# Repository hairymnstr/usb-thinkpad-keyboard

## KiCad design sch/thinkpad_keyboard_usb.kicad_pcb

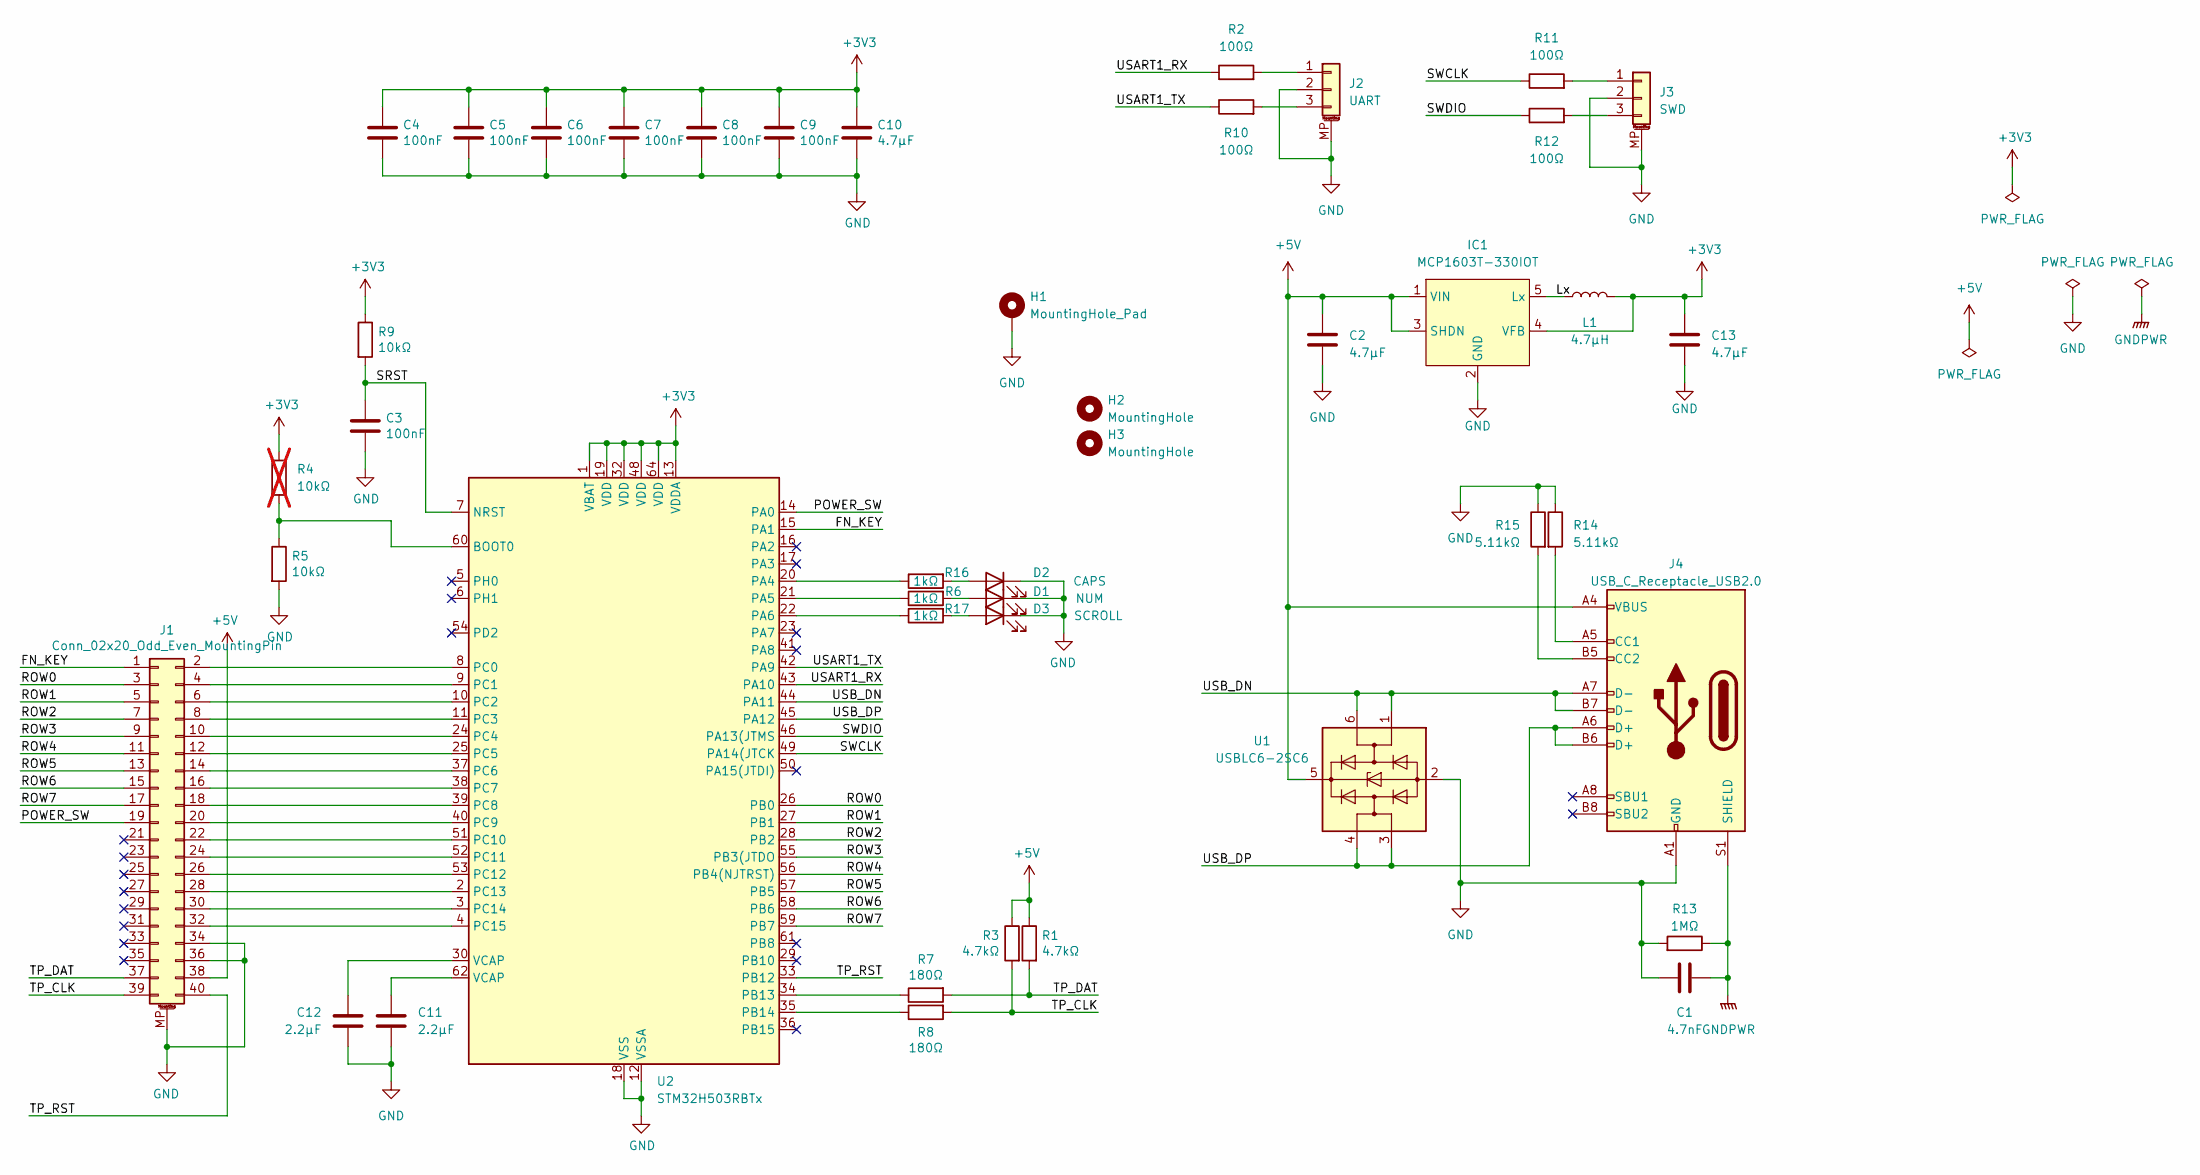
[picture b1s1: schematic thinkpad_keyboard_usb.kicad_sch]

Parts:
C1: 4.7nF; C_0805_2012Metric
C2, C10, C13: 4.7µF; C_0805_2012Metric
C3, C4, C5, C6, C7, C8, C9: 100nF; C_0603_1608Metric
C11, C12: 2.2µF; C_0603_1608Metric
D1: NUM; D_0603_1608Metric
D2: CAPS; D_0603_1608Metric
D3: SCROLL; D_0603_1608Metric
H1: MountingHole_Pad; MountingHole_2.2mm_M2_Pad
H2, H3: MountingHole; MountingHole_3.2mm_M3
IC1: MCP1603T-330IOT; TSOT-23-5
J1: Conn_02x20_Odd_Even_MountingPin; MOLEX_SLIMSTACK_54363_02x20_P0.5mm
J2: UART; JST_SH_SM03B-SRSS-TB_1x03-1MP_P1.00mm_Horizontal
J3: SWD; JST_SH_SM03B-SRSS-TB_1x03-1MP_P1.00mm_Horizontal
J4: USB_C_Receptacle_USB2.0; USB_C_Receptacle_GCT_USB4085
L1: 4.7µH; L_Wuerth_WE-TPC-3816
R1, R3: 4.7kΩ; R_0603_1608Metric
R2, R10, R11, R12: 100Ω; R_0603_1608Metric
R4: 10kΩ; R_0603_1608Metric; not fitted
R5, R9: 10kΩ; R_0603_1608Metric
R6, R16, R17: 1kΩ; R_0603_1608Metric
R7, R8: 180Ω; R_0603_1608Metric
R13: 1MΩ; R_0603_1608Metric
R14, R15: 5.11kΩ; R_0603_1608Metric
U1: USBLC6-2SC6; SOT-23-6
U2: STM32H503RBTx; LQFP-64_10x10mm_P0.5mm

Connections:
+3V3: C4.1, C5.1, C6.1, C7.1, C8.1, C9.1, C10.1, C13.1, IC1.4 (VFB), L1.2, R4.1, R9.1, U2.1 (VBAT), U2.13 (VDDA), U2.19 (VDD), U2.32 (VDD), U2.48 (VDD), U2.64 (VDD)
+5V: C2.1, IC1.1 (VIN), IC1.3 (SHDN), J1.38, J4.A4 (VBUS), J4.A9 (VBUS), J4.B4 (VBUS), J4.B9 (VBUS), R1.1, R3.1, U1.5 (VBUS)
/FN_KEY: J1.1, U2.15 (PA1)
/Lx: IC1.5 (Lx), L1.1
/POWER_SW: J1.19, U2.14 (PA0)
/ROW0: J1.3, U2.26 (PB0)
/ROW1: J1.5, U2.27 (PB1)
/ROW2: J1.7, U2.28 (PB2)
/ROW3: J1.9, U2.55 (PB3(JTDO)
/ROW4: J1.11, U2.56 (PB4(NJTRST))
/ROW5: J1.13, U2.57 (PB5)
/ROW6: J1.15, U2.58 (PB6)
/ROW7: J1.17, U2.59 (PB7)
/SRST: C3.1, R9.2, U2.7 (NRST)
/SWCLK: R11.1, U2.49 (PA14(JTCK)
/SWDIO: R12.1, U2.46 (PA13(JTMS)
/TP_CLK: J1.39, R3.2, R8.2
/TP_DAT: J1.37, R1.2, R7.2
/TP_RST: J1.40, U2.33 (PB12)
/USART1_RX: R2.1, U2.43 (PA10)
/USART1_TX: R10.1, U2.42 (PA9)
/USB_DN: J4.A7 (D-), J4.B7 (D-), U1.1 (I/O1), U1.6 (I/O1), U2.44 (PA11)
/USB_DP: J4.A6 (D+), J4.B6 (D+), U1.3 (I/O2), U1.4 (I/O2), U2.45 (PA12)
GND: C1.2, C2.2, C3.2, C4.2, C5.2, C6.2, C7.2, C8.2, C9.2, C10.2, C11.2, C12.2, C13.2, D1.1 (K), D2.1 (K), D3.1 (K), H1.1, IC1.2 (GND), J1.34, J1.36, J1.MP (MountPin), J2.2, J2.MP (MountPin), J3.2, J3.MP (MountPin), J4.A1 (GND), J4.A12 (GND), J4.B1 (GND), J4.B12 (GND), R5.2, R13.2, R14.1, R15.1, U1.2 (GND), U2.12 (VSSA), U2.18 (VSS), U2.31 (VSS), U2.47 (VSS), U2.63 (VSS)
GNDPWR: C1.1, J4.S1 (SHIELD), R13.1
unnamed: C11.1, U2.62 (VCAP)
unnamed: C12.1, U2.30 (VCAP)
unnamed: D1.2 (A), R6.2
unnamed: D2.2 (A), R16.2
unnamed: D3.2 (A), R17.2
unnamed: J1.2, U2.8 (PC0)
unnamed: J1.4, U2.9 (PC1)
unnamed: J1.6, U2.10 (PC2)
unnamed: J1.8, U2.11 (PC3)
unnamed: J1.10, U2.24 (PC4)
unnamed: J1.12, U2.25 (PC5)
unnamed: J1.14, U2.37 (PC6)
unnamed: J1.16, U2.38 (PC7)
unnamed: J1.18, U2.39 (PC8)
unnamed: J1.20, U2.40 (PC9)
unnamed: J1.22, U2.51 (PC10)
unnamed: J1.24, U2.52 (PC11)
unnamed: J1.26, U2.53 (PC12)
unnamed: J1.28, U2.2 (PC13)
unnamed: J1.30, U2.3 (PC14)
unnamed: J1.32, U2.4 (PC15)
unnamed: J2.1, R2.2
unnamed: J2.3, R10.2
unnamed: J3.1, R11.2
unnamed: J3.3, R12.2
unnamed: J4.A5 (CC1), R14.2
unnamed: J4.B5 (CC2), R15.2
unnamed: R4.2, R5.1, U2.60 (BOOT0)
unnamed: R16.1, U2.20 (PA4)
unnamed: R6.1, U2.21 (PA5)
unnamed: R17.1, U2.22 (PA6)
unnamed: R7.1, U2.34 (PB13)
unnamed: R8.1, U2.35 (PB14)

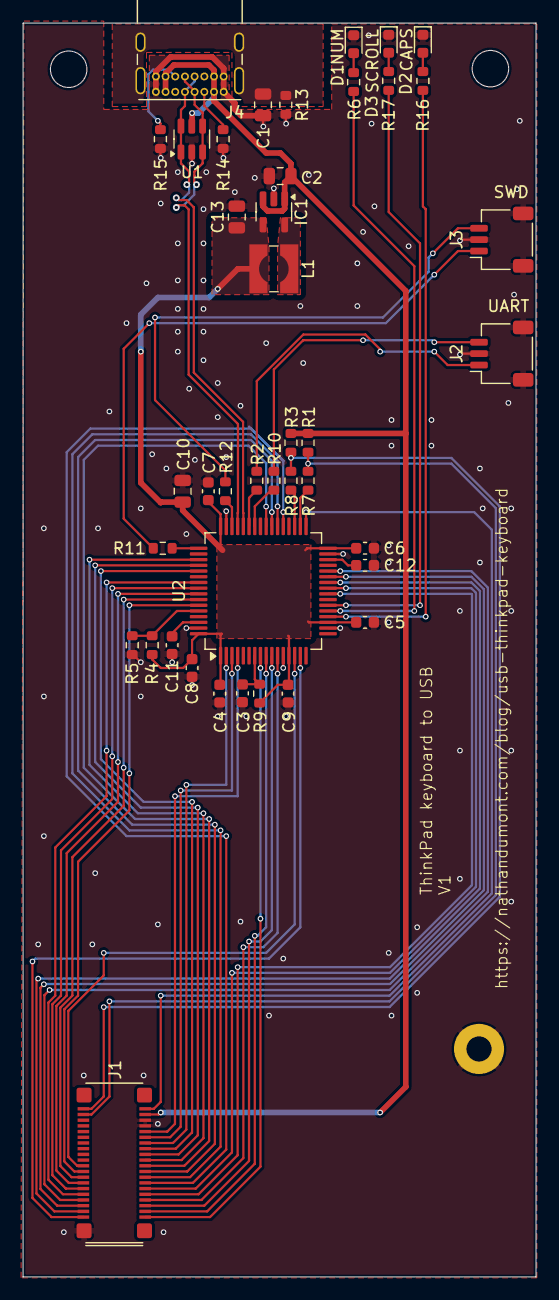
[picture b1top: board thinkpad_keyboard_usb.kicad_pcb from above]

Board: 2 copper layers, 45.0 x 110.0 mm, 44 parts (0 on the bottom side), 58 nets.

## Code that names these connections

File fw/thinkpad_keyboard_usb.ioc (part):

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Mcu.Name=STM32H503RBTx
Mcu.Package=LQFP64
Mcu.UserName=STM32H503RBTx
PA0.GPIOParameters=GPIO_Label
PA0.GPIO_Label=POWER_SW
PA0.Signal=GPIO_Input
PA1.GPIOParameters=GPIO_Label
PA1.GPIO_Label=FN_KEY
PA1.Signal=GPIO_Input
PA10.Mode=Asynchronous
PA10.Signal=USART1_RX
PA11.Mode=Device
PA11.Signal=USB_DM
PA12.Mode=Device
PA12.Signal=USB_DP
PA13(JTMS/SWDIO).Mode=Serial_Wire
PA13(JTMS/SWDIO).Signal=DEBUG_JTMS-SWDIO
PA14(JTCK/SWCLK).Mode=Serial_Wire
PA14(JTCK/SWCLK).Signal=DEBUG_JTCK-SWCLK
PA5.GPIOParameters=GPIO_Label
PA5.GPIO_Label=LED
PA5.Signal=GPIO_Output
PA9.Mode=Asynchronous
PA9.Signal=USART1_TX
PB0.Signal=GPIO_Output
PB1.Signal=GPIO_Output
PB12.GPIOParameters=GPIO_Label
PB12.GPIO_Label=TP_RST
PB12.Signal=GPIO_Output
PB13.GPIOParameters=GPIO_Label
PB13.GPIO_Label=TP_DAT
PB13.Signal=GPIO_Input
PB14.GPIOParameters=GPIO_Label
PB14.GPIO_Label=TP_CLK
PB14.Signal=GPIO_Output
PB15.GPIOParameters=GPIO_Label
PB15.GPIO_Label=FN_KEY
PB15.Signal=GPIO_Input
PB2.Signal=GPIO_Output
PB3(JTDO/TRACESWO).Signal=GPIO_Output
PB4(NJTRST).Signal=GPIO_Output
PB5.Signal=GPIO_Output
PB6.Signal=GPIO_Output
PB7.Signal=GPIO_Output
PC0.Signal=GPIO_Input
PC1.Signal=GPIO_Input
PC10.Signal=GPIO_Input
PC11.Signal=GPIO_Input
PC12.Signal=GPIO_Input
PC13.Signal=GPIO_Input
PC14-OSC32_IN(OSC32_IN).Signal=GPIO_Input
PC15-OSC32_OUT(OSC32_OUT).Signal=GPIO_Input
PC2.Signal=GPIO_Input
PC3.Signal=GPIO_Input
PC4.Signal=GPIO_Input
PC5.Signal=GPIO_Input
PC6.Signal=GPIO_Input
PC7.Signal=GPIO_Input
PC8.Signal=GPIO_Input
PC9.Signal=GPIO_Input
RCC.HSE_VALUE=25000000
RCC.SYSCLKFreq_VALUE=32000000
board=custom

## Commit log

2025-03-06 Initial commit, board design done but mech layout might need improving
2025-03-06 Added board name and version to silk
